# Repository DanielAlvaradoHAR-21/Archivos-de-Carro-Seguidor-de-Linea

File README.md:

# Archivos-de-Carro-Seguidor-de-Linea
En la carpeta se encuentran El Prototipo, Programación en Arduino, Los Archivos Eagle del puente H y de los sensores

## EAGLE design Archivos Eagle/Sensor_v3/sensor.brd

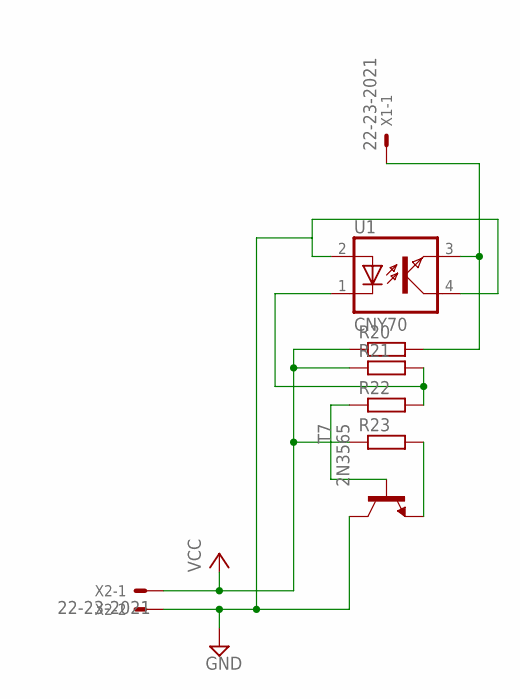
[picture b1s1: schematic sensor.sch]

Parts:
R20, R21, R22, R23: R-EU_0204/7; 0204/7
T7: 2N3565; TO92
U1: CNY70
X1, X2: 22-23-2021

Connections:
GND1: T7.1 (C), U1.2, U1.4, X2.2
unnamed: R23.2, T7.3 (E)
unnamed: R21.2, R22.2, U1.1
unnamed: R20.2, U1.3, X1.1
unnamed: R22.1, T7.2 (B)
VCC: R20.1, R21.1, R23.1, X2.1

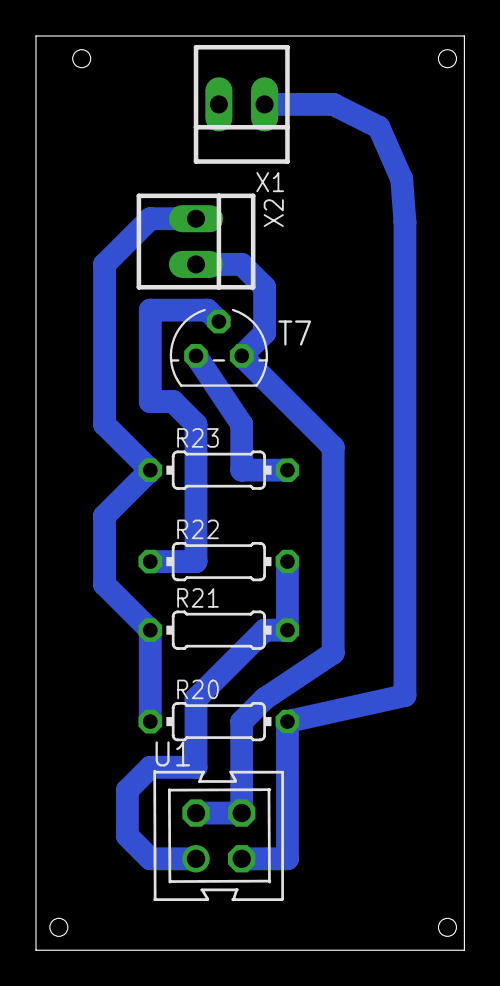
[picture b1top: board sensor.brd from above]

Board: 2 copper layers, 23.8 x 50.8 mm, 8 parts (0 on the bottom side), 6 nets.

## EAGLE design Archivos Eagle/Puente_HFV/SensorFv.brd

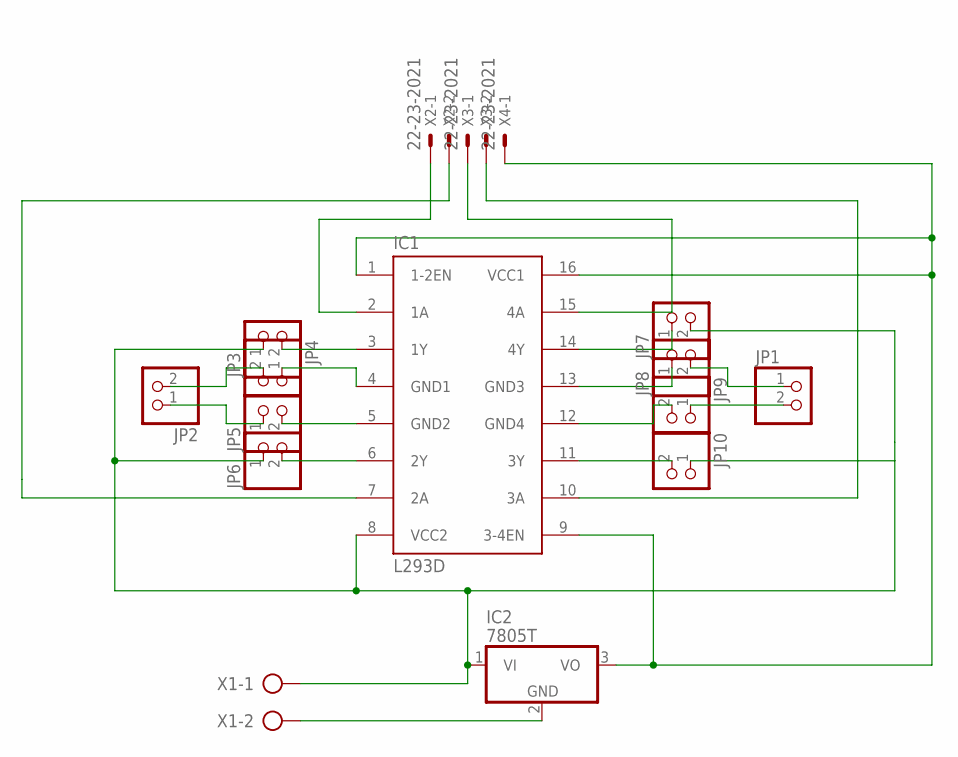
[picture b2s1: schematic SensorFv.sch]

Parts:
IC1: L293D; DIL16
IC2: 7805T; TO220H
JP1, JP2, JP3, JP4, JP5, JP6, JP7, JP8, JP9, JP10: PINHD-1X2; 1X02
X1: AK500/2-H
X2, X3, X4: 22-23-2021

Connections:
unnamed: IC1.3 (1Y), JP3.2
unnamed: JP2.2, JP4.2
unnamed: IC1.4 (GND1), JP4.1
unnamed: JP2.1, JP5.1
unnamed: IC1.5 (GND2), JP5.2
unnamed: IC1.6 (2Y), JP6.2
unnamed: IC1.14 (4Y), JP7.1
unnamed: IC1.13 (GND3), JP8.1
unnamed: IC1.12 (GND4), JP9.2
unnamed: IC1.11 (3Y), JP10.2
unnamed: JP1.1, JP8.2
unnamed: JP1.2, JP9.1
unnamed: IC1.2 (1A), X2.1
unnamed: IC1.7 (2A), X2.2
unnamed: IC1.15 (4A), X3.1
unnamed: IC1.10 (3A), X3.2
unnamed: IC1.8 (VCC2), IC2.1 (VI), JP3.1, JP6.1, JP7.2, JP10.1, X1.1
unnamed: IC1.1 (1-2EN), IC1.9 (3-4EN), IC1.16 (VCC1), IC2.3 (VO), X4.1
unnamed: IC2.2 (GND), X1.2

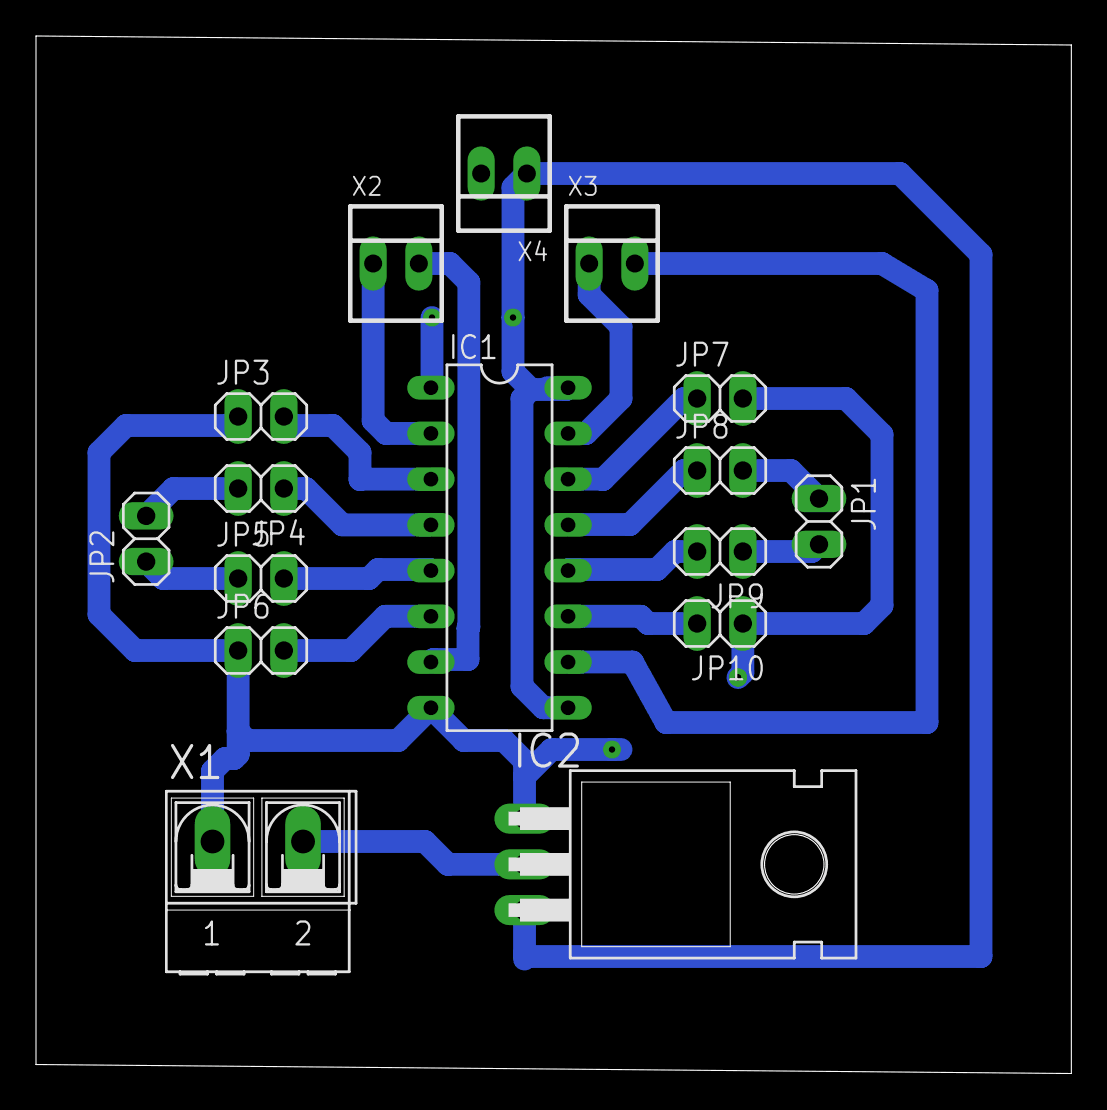
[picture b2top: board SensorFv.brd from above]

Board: 2 copper layers, 57.5 x 57.6 mm, 16 parts (0 on the bottom side), 19 nets.

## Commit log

2018-06-07 Carpetas
